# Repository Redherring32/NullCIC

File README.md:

# NullCIC
A little board to replace the CIC on the original NES or [OpenTendo](https://github.com/Redherring32/OpenTendo), and restore reset functionality.

All the files needed to make your own are located under the releases section.

You can also do the same thing the NullCIC does manually, just check "Reset fix without NullCIC.jpg"

Licensed under the TAPR Open Hardware License (www.tapr.org/OHL)

©Redherring32 2019-2020

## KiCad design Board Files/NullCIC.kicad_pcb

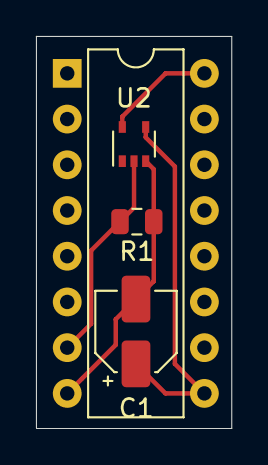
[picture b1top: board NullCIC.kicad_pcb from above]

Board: 2 copper layers, 10.8 x 21.8 mm, 4 parts (0 on the bottom side), 4 nets.

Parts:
 : 10NES_CIC; DIP-16_W7.62mm
C1: 0.47uF; CP_Elec_4x5.3
R1: 0R; R_0805_2012Metric
U2: 74LVC1GU04DRL; SOT-353_SC-70-5

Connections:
/GND: .8, C1.2, R1.1, U2.3
/RST-In: .7, R1.2, U2.2
/RST-Out: .9, C1.1, U2.4
/VCC: .16, U2.5

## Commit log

2020-03-06 Added OpenTendo link
2020-03-06 Added License
2020-03-06 Added license notice
2020-03-10 Added board files
2020-08-10 +Added Schematic symbol library +Added sym-lib-table to make importing into KiCad easier +Added image to README.md +Added guide for manual reset fix +Corrected resistor value error in NullCIC.sch
2020-08-10 +Fixed some issues with Reset fix without NullCIC.jpg
